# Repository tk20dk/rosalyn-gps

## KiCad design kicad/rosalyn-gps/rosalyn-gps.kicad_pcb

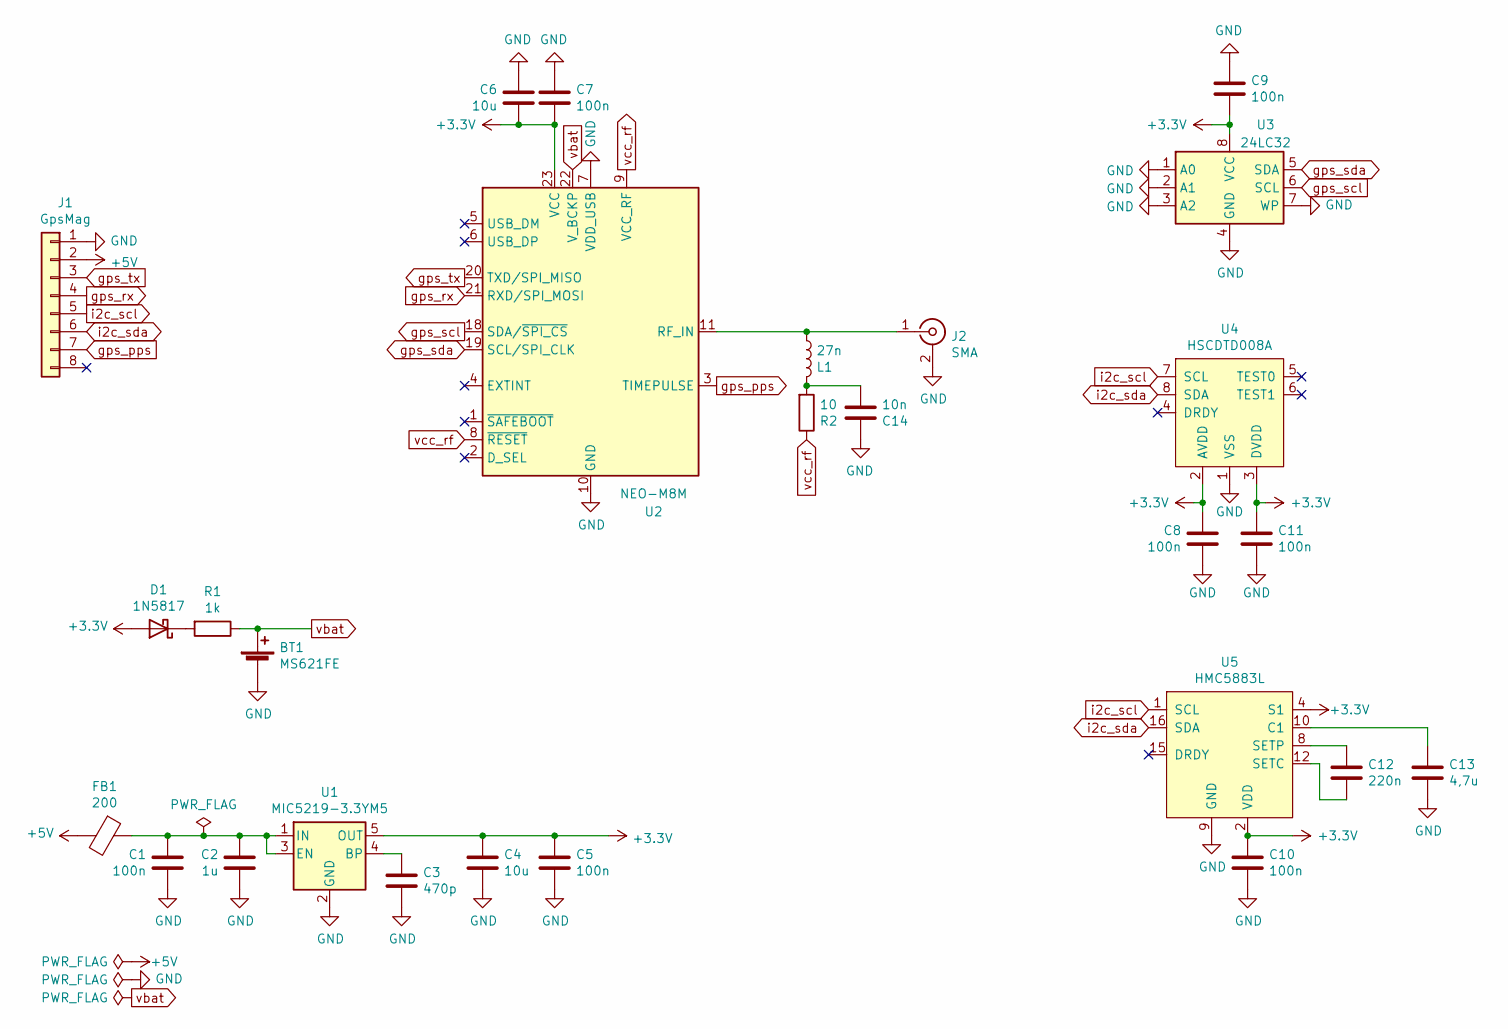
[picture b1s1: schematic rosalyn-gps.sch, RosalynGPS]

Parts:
BT1: MS621FE
C1, C5, C7, C8, C9, C10, C11: 100n; C_0603_1608Metric
C2: 1u; C_0805_2012Metric
C3: 470p; C_0603_1608Metric
C4, C6: 10u; C_0805_2012Metric
C12: 220n; C_0603_1608Metric
C13: 4,7u; C_0805_2012Metric
C14: 10n; C_0603_1608Metric
D1: 1N5817; D_SOD-323
FB1: 200; L_0603_1608Metric
J1: GpsMag; JST_SH_SM08B-SRSS-TB_1x08-1MP_P1.00mm_Horizontal
J2: SMA; SMA_Wurth_60312002114503_Vertical
L1: 27n; L_0603_1608Metric
R1: 1k; R_0603_1608Metric
R2: 10; R_0603_1608Metric
U1: MIC5219-3.3YM5; SOT-23-5
U2: NEO-M8M; ublox_NEO
U3: 24LC32; SOIC-8_3.9x4.9mm_P1.27mm
U4: HSCDTD008A
U5: HMC5883L

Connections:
+3V3: C4.2, C5.2, C6.1, C7.2, C8.2, C9.2, C10.1, C11.1, D1.2 (A), U1.5 (OUT), U2.23 (VCC), U3.8 (VCC), U4.2 (AVDD), U4.3 (DVDD), U5.2 (VDD), U5.4 (S1)
+5V: FB1.2, J1.2
GND: BT1.2 (-), C1.1, C2.1, C3.1, C4.1, C5.1, C6.2, C7.1, C8.1, C9.1, C10.2, C11.2, C13.2, C14.1, J1.1, J2.2 (Ext), U1.2 (GND), U2.7 (VDD_USB), U2.10 (GND), U2.12 (GND), U2.13 (GND), U2.24 (GND), U3.1 (A0), U3.2 (A1), U3.3 (A2), U3.4 (GND), U3.7 (WP), U4.1 (VSS), U5.9 (GND), U5.13 (GND)
unnamed: C1.2, C2.2, FB1.1, U1.1 (IN), U1.3 (EN)
unnamed: C3.2, U1.4 (BP)
unnamed: C12.1, U5.8 (SETP)
unnamed: C12.2, U5.12 (SETC)
unnamed: C13.1, U5.10 (C1)
unnamed: C14.2, L1.1, R2.2
unnamed: D1.1 (K), R1.2
unnamed: J2.1 (In), L1.2, U2.11 (RF_IN)
gps_pps: J1.7, U2.3 (TIMEPULSE)
gps_rx: J1.4, U2.21 (RXD/SPI_MOSI)
gps_scl: U2.18 (SDA/~SPI_CS), U3.6 (SCL)
gps_sda: U2.19 (SCL/SPI_CLK), U3.5 (SDA)
gps_tx: J1.3, U2.20 (TXD/SPI_MISO)
i2c_scl: J1.5, U4.7 (SCL), U5.1 (SCL)
i2c_sda: J1.6, U4.8 (SDA), U5.16 (SDA)
vbat: BT1.1 (+), R1.1, U2.22 (V_BCKP)
vcc_rf: R2.1, U2.8 (~RESET), U2.9 (VCC_RF)

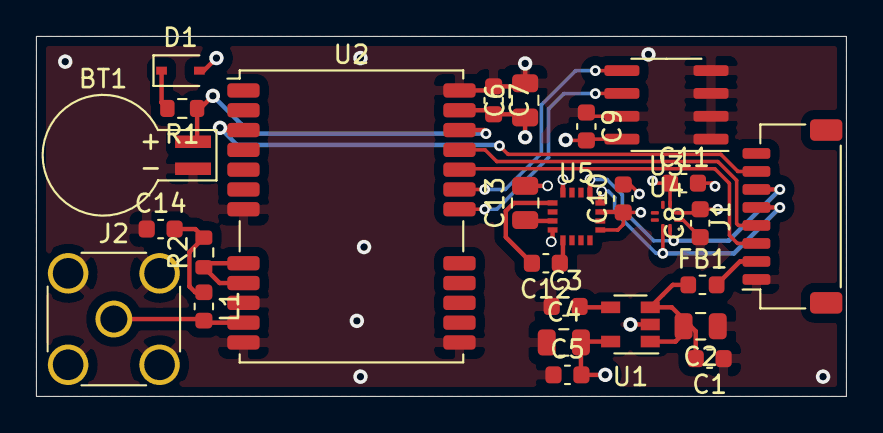
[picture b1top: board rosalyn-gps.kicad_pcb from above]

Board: 4 copper layers, 45.0 x 20.0 mm, 27 parts (0 on the bottom side), 20 nets.

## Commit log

2020-12-29 added documents
2020-12-29 initial schematic done
2020-12-29 initial pcb layout
2020-12-29 cleanup pcb layout
